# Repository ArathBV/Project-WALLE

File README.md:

# Project-WALLE
## Authors: Arath Villanueva, Devon Bolt
### Repository Overview
- This repository contains a folder of Doxygen items, WALL-E source code found in Codes, and Hardware Design aspects both mechanical and electrical in the Hardware folder.
### Project Website and Documentation
Project in depth details and website https://arathbv.github.io/Project-WALLE/index.html

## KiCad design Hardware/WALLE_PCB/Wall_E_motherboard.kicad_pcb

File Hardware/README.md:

# WALL-E Hardware Files
- This folder contains the Mechanical design files and the PCB design files. 
- The Mechanical desing components were changed based on the electronic and peripherals that were used for this WALL-E project.
- The WALL-E PCB Folder contains the WALL-E motheboard that was created for this project
- All original and remaining WALL-E CAD and step files can be found at https://wired.chillibasket.com/3d-printed-wall-e/

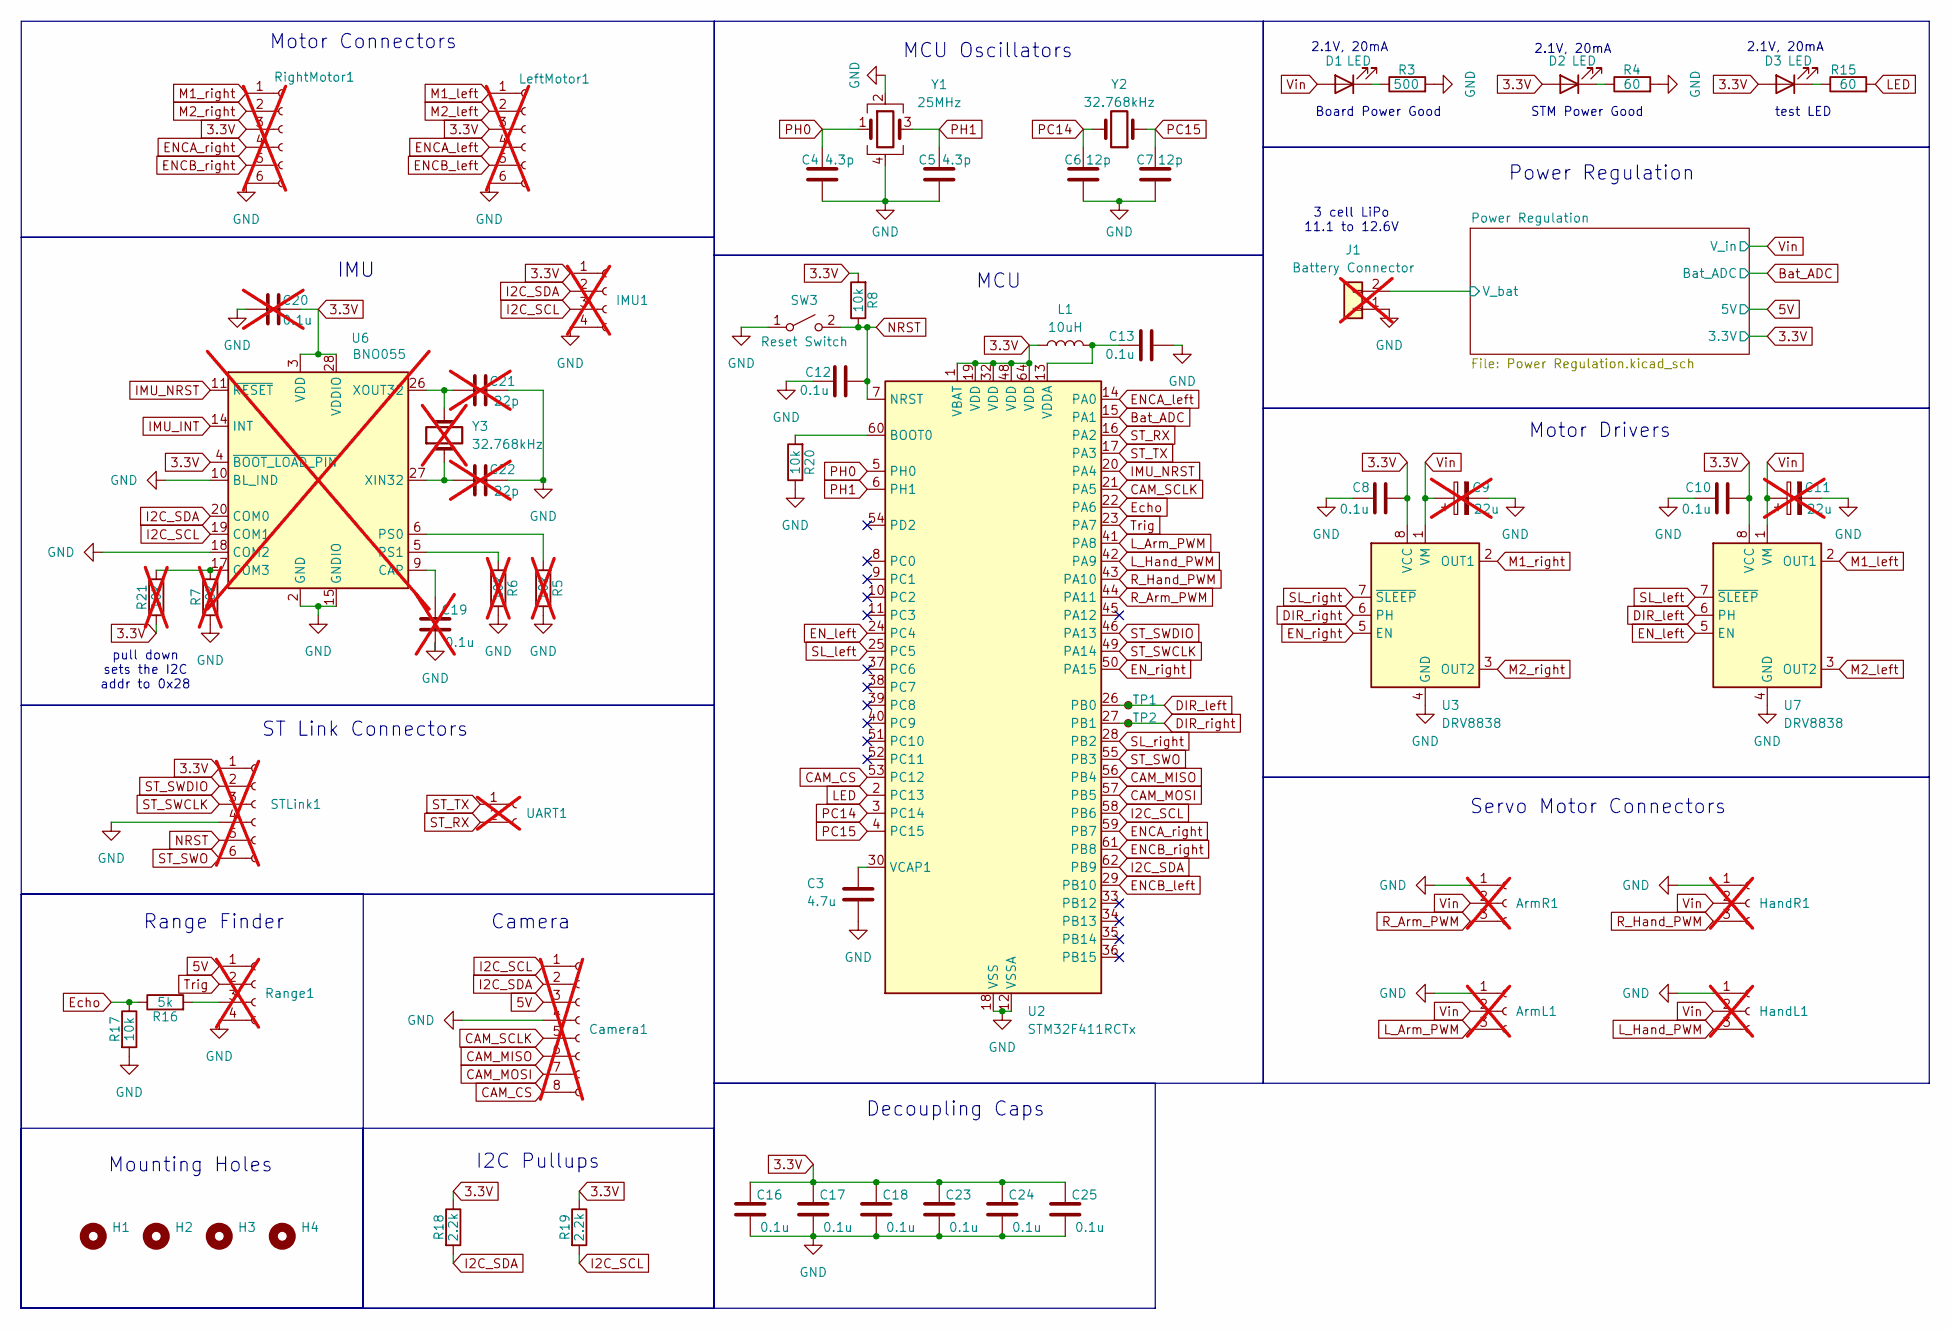
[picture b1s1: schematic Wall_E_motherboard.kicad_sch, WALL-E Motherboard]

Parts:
ArmL1: Conn_01x03_Socket; PinHeader_1x03_P2.54mm_Vertical; not fitted
ArmR1: Conn_01x03_Socket; PinHeader_1x03_P2.54mm_Vertical; not fitted
C3: 4.7u; C_0603_1608Metric
C4, C5: 4.3p; C_0603_1608Metric
C6, C7: 12p; C_0603_1608Metric
C8, C10, C12, C13, C16, C17, C18, C23, C24, C25: 0.1u; C_0603_1608Metric
C9, C11: 22u; CP_Radial_D5.0mm_P2.00mm; not fitted
C19, C20: 0.1u; C_0603_1608Metric; not fitted
C21, C22: 22p; C_0603_1608Metric; not fitted
Camera1: Conn_01x08_Socket; PinHeader_1x08_P2.54mm_Vertical; not fitted
D1, D2, D3: LED; LED_0603_1608Metric
H1, H2, H3, H4: MountingHole; MountingHole_3.2mm_M3
HandL1: Conn_01x03_Socket; PinHeader_1x03_P2.54mm_Vertical; not fitted
HandR1: Conn_01x03_Socket; PinHeader_1x03_P2.54mm_Vertical; not fitted
IMU1: Conn_01x04_Socket; PinHeader_1x04_P2.54mm_Vertical; not fitted
J1: Conn_01x02; AMASS_XT30PW-M_1x02_P2.50mm_Horizontal; not fitted
L1: 10uH; L_1008_2520Metric
LeftMotor1: Conn_01x06_Socket; PinHeader_1x06_P2.54mm_Vertical; not fitted
R3: 500; R_0603_1608Metric
R4, R15: 60; R_0603_1608Metric
R5, R6, R7, R21: 10k; R_0603_1608Metric; not fitted
R8, R17, R20: 10k; R_0603_1608Metric
R16: 5k; R_0603_1608Metric
R18, R19: 2.2k; R_0603_1608Metric
Range1: Conn_01x04_Socket; PinHeader_1x04_P2.54mm_Vertical; not fitted
RightMotor1: Conn_01x06_Socket; PinHeader_1x06_P2.54mm_Vertical; not fitted
STLink1: Conn_01x06_Socket; PinHeader_1x06_P2.54mm_Horizontal; not fitted
SW3: SW_SPST; SW_SPST_PTS645
TP1, TP2: TestPoint_Small; TestPoint_Pad_D1.0mm
U2: STM32F411RCTx; LQFP-64_10x10mm_P0.5mm
U3, U7: DRV8838; WSON-8-1EP_2x2mm_P0.5mm_EP0.9x1.6mm
U6: BNO055; LGA-28_5.2x3.8mm_P0.5mm; not fitted
UART1: Conn_01x02_Socket; PinHeader_1x02_P2.54mm_Horizontal; not fitted
Y1: 25MHz; Crystal_SMD_3225-4Pin_3.2x2.5mm
Y2: 32.768kHz; Crystal_SMD_3215-2Pin_3.2x1.5mm
Y3: 32.768kHz; Crystal_SMD_3215-2Pin_3.2x1.5mm; not fitted

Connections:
3.3V: C8.1, C10.1, C16.1, C17.1, C18.1, C20.2, C23.1, C24.1, C25.1, D2.2 (A), D3.2 (A), IMU1.1, L1.1, LeftMotor1.3, R8.2, R18.1, R19.1, R21.2, RightMotor1.3, STLink1.1, U2.1 (VBAT), U2.19 (VDD), U2.32 (VDD), U2.48 (VDD), U2.64 (VDD), U3.8 (VCC), U6.3 (VDD), U6.4 (~BOOT_LOAD_PIN), U6.28 (VDDIO), U7.8 (VCC); also elsewhere on the board
5V: Camera1.3, Range1.1; also elsewhere on the board
/Power Regulation/V_bat: J1.2; also elsewhere on the board
Bat_ADC: U2.15 (PA1); also elsewhere on the board
CAM_CS: Camera1.8, U2.53 (PC12)
CAM_MISO: Camera1.6, U2.56 (PB4)
CAM_MOSI: Camera1.7, U2.57 (PB5)
CAM_SCLK: Camera1.5, U2.21 (PA5)
DIR_left: TP1.1, U2.26 (PB0), U7.6 (PH)
DIR_right: TP2.1, U2.27 (PB1), U3.6 (PH)
ENCA_left: LeftMotor1.4, U2.14 (PA0)
ENCA_right: RightMotor1.4, U2.59 (PB7)
ENCB_left: LeftMotor1.5, U2.29 (PB10)
ENCB_right: RightMotor1.5, U2.61 (PB8)
EN_left: U2.24 (PC4), U7.5 (EN)
EN_right: U2.50 (PA15), U3.5 (EN)
Echo: R16.1, R17.1, U2.22 (PA6)
GND: ArmL1.1, ArmR1.1, C3.2, C4.2, C5.2, C6.2, C7.2, C8.2, C9.2, C10.2, C11.2, C12.2, C13.2, C16.2, C17.2, C18.2, C19.2, C20.1, C21.2, C22.2, C23.2, C24.2, C25.2, Camera1.4, HandL1.1, HandR1.1, IMU1.4, J1.1, LeftMotor1.6, R3.2, R4.2, R5.1, R6.1, R7.2, R17.2, R20.1, Range1.4, RightMotor1.6, STLink1.4, SW3.1 (A), U2.12 (VSSA), U2.18 (VSS), U2.31 (VSS), U2.47 (VSS), U2.63 (VSS), U3.4 (GND), U3.9 (GND), U6.2 (GND), U6.10 (BL_IND), U6.15 (GNDIO), U6.16 (GNDIO), U6.18 (COM2), U6.25 (GNDIO), U7.4 (GND), U7.9 (GND), Y1.2, Y1.4; also elsewhere on the board
I2C_SCL: Camera1.1, IMU1.3, R19.2, U2.58 (PB6), U6.19 (COM1)
I2C_SDA: Camera1.2, IMU1.2, R18.2, U2.62 (PB9), U6.20 (COM0)
IMU_INT: U6.14 (INT)
IMU_NRST: U2.20 (PA4), U6.11 (~RESET)
LED: R15.2, U2.2 (PC13)
L_Arm_PWM: ArmL1.3, U2.41 (PA8)
L_Hand_PWM: HandL1.3, U2.42 (PA9)
M1_left: LeftMotor1.1, U7.2 (OUT1)
M1_right: RightMotor1.1, U3.2 (OUT1)
M2_left: LeftMotor1.2, U7.3 (OUT2)
M2_right: RightMotor1.2, U3.3 (OUT2)
NRST: C12.1, R8.1, STLink1.5, SW3.2 (B), U2.7 (NRST)
unnamed: D1.1 (K), R3.1
unnamed: D2.1 (K), R4.1
unnamed: D3.1 (K), R15.1
unnamed: R16.2, Range1.3
unnamed: R20.2, U2.60 (BOOT0)
unnamed: C3.1, U2.30 (VCAP1)
unnamed: C13.1, L1.2, U2.13 (VDDA)
unnamed: C19.1, U6.9 (CAP)
unnamed: R7.1, R21.1, U6.17 (COM3)
unnamed: R5.2, U6.6 (PS0)
unnamed: R6.2, U6.5 (PS1)
unnamed: C22.1, U6.27 (XIN32), Y3.1
unnamed: C21.1, U6.26 (XOUT32), Y3.2
PC14: C6.1, U2.3 (PC14), Y2.2
PC15: C7.1, U2.4 (PC15), Y2.1
PH0: C4.1, U2.5 (PH0), Y1.1
PH1: C5.1, U2.6 (PH1), Y1.3
R_Arm_PWM: ArmR1.3, U2.44 (PA11)
R_Hand_PWM: HandR1.3, U2.43 (PA10)
SL_left: U2.25 (PC5), U7.7 (~SLEEP)
SL_right: U2.28 (PB2), U3.7 (~SLEEP)
ST_RX: U2.16 (PA2), UART1.2
ST_SWCLK: STLink1.3, U2.49 (PA14)
ST_SWDIO: STLink1.2, U2.46 (PA13)
ST_SWO: STLink1.6, U2.55 (PB3)
ST_TX: U2.17 (PA3), UART1.1
Trig: Range1.2, U2.23 (PA7)
Vin: ArmL1.2, ArmR1.2, C9.1, C11.1, D1.2 (A), HandL1.2, HandR1.2, U3.1 (VM), U7.1 (VM); also elsewhere on the board

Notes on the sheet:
Decoupling Caps
STM Power Good
Board Power Good
Range Finder
Power Regulation
Mounting Holes
Camera
MCU Oscillators
Motor Connectors
Servo Motor Connectors
ST Link Connectors
2.1V, 20mA
IMU
Motor Drivers
I2C Pullups
3 cell LiPo 11.1 to 12.6V
test LED
pull down sets the I2C addr to 0x28
MCU

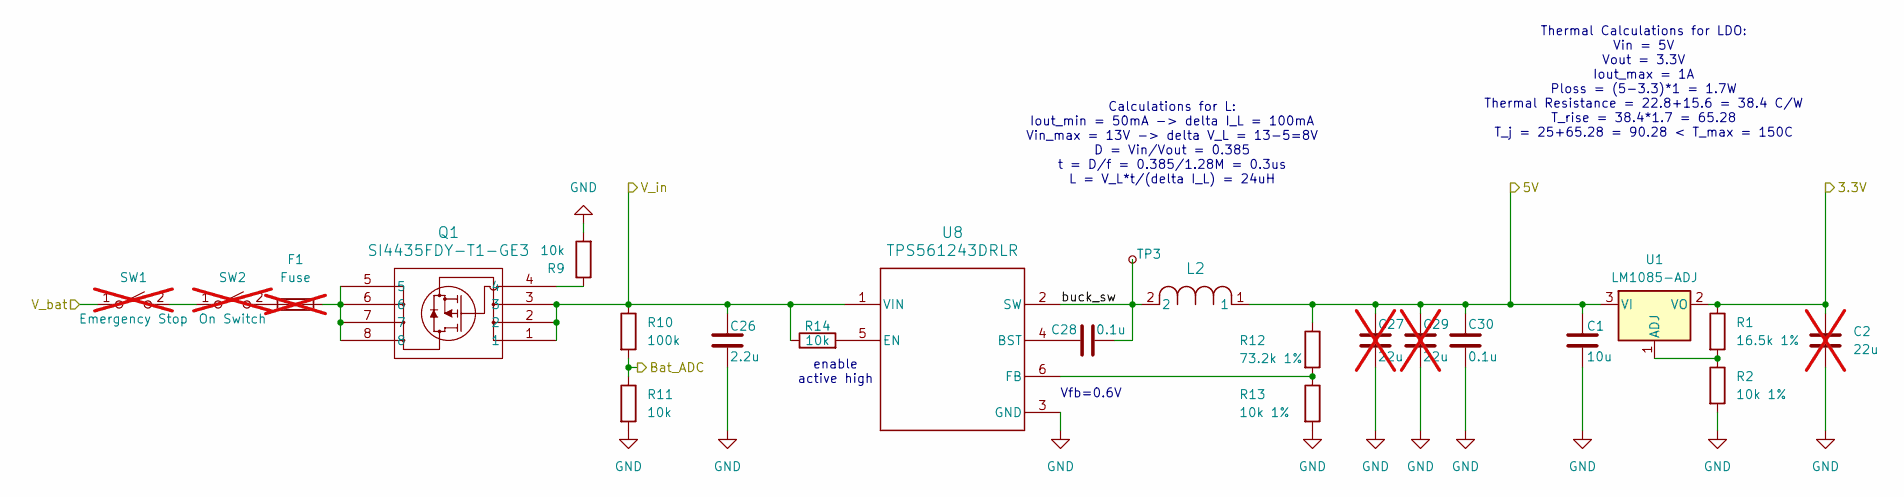
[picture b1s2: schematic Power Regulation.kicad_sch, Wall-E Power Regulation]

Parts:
C1: 10u; C_0603_1608Metric
C2, C27, C29: 22u; CP_Radial_D5.0mm_P2.00mm; not fitted
C26: 2.2u; C_0603_1608Metric
C28, C30: 0.1u; C_0603_1608Metric
F1: Fuse; Fuseholder_Blade_Mini_Keystone_3568; not fitted
L2: IFDC5050HZER270M; IND_IFDC5050HZER_VIS
Q1: SI4435FDY-T1-GE3; SO-8_VIS
R1: 16.5k 1%; R_0603_1608Metric
R2, R13: 10k 1%; R_0603_1608Metric
R9, R11, R14: 10k; R_0603_1608Metric
R10: 100k; R_0603_1608Metric
R12: 73.2k 1%; R_0603_1608Metric
SW1, SW2: SW_SPST; AMASS_XT30PW-F_1x02_P2.50mm_Horizontal; not fitted
TP3: TestPoint_Small; TestPoint_Pad_D1.0mm
U1: LM1085-ADJ; TO-263-3_TabPin2
U8: TPS561243DRLR; DRL0006A-MFG

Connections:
3.3V: C2.1, R1.1, U1.2 (VO); also elsewhere on the board
5V: C1.1, C27.1, C29.1, C30.1, L2.1, R12.1, U1.3 (VI); also elsewhere on the board
/Power Regulation/V_bat: SW1.1 (A); also elsewhere on the board
/Power Regulation/buck_sw: C28.2, L2.2, TP3.1, U8.2 (SW)
Bat_ADC: R10.2, R11.1; also elsewhere on the board
GND: C1.2, C2.2, C26.2, C27.2, C29.2, C30.2, R2.2, R9.2, R11.2, R13.2, U8.3 (GND); also elsewhere on the board
unnamed: F1.2, Q1.5, Q1.6, Q1.7, Q1.8
unnamed: Q1.4, R9.1
unnamed: SW1.2 (B), SW2.1 (A)
unnamed: F1.1, SW2.2 (B)
unnamed: R1.2, R2.1, U1.1 (ADJ)
unnamed: C28.1, U8.4 (BST)
unnamed: R14.2, U8.5 (EN)
unnamed: R12.2, R13.1, U8.6 (FB)
Vin: C26.1, Q1.1, Q1.2, Q1.3, R10.1, R14.1, U8.1 (VIN); also elsewhere on the board

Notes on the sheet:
Vfb=0.6V
Calculations for L: Iout_min = 50mA -> delta I_L = 100mA Vin_max = 13V -> delta V_L = 13-5=8V D = Vin/Vout = 0.385 t = D/f = 0.385/1.28M = 0.3us L = V_L*t/(delta I_L) = 24uH
enable active high
Thermal Calculations for LDO: Vin = 5V Vout = 3.3V Iout_max = 1A Ploss = (5-3.3)*1 = 1.7W Thermal Resistance = 22.8+15.6 = 38.4 C/W T_rise = 38.4*1.7 = 65.28 T_j = 25+65.28 = 90.28 < T_max = 150C

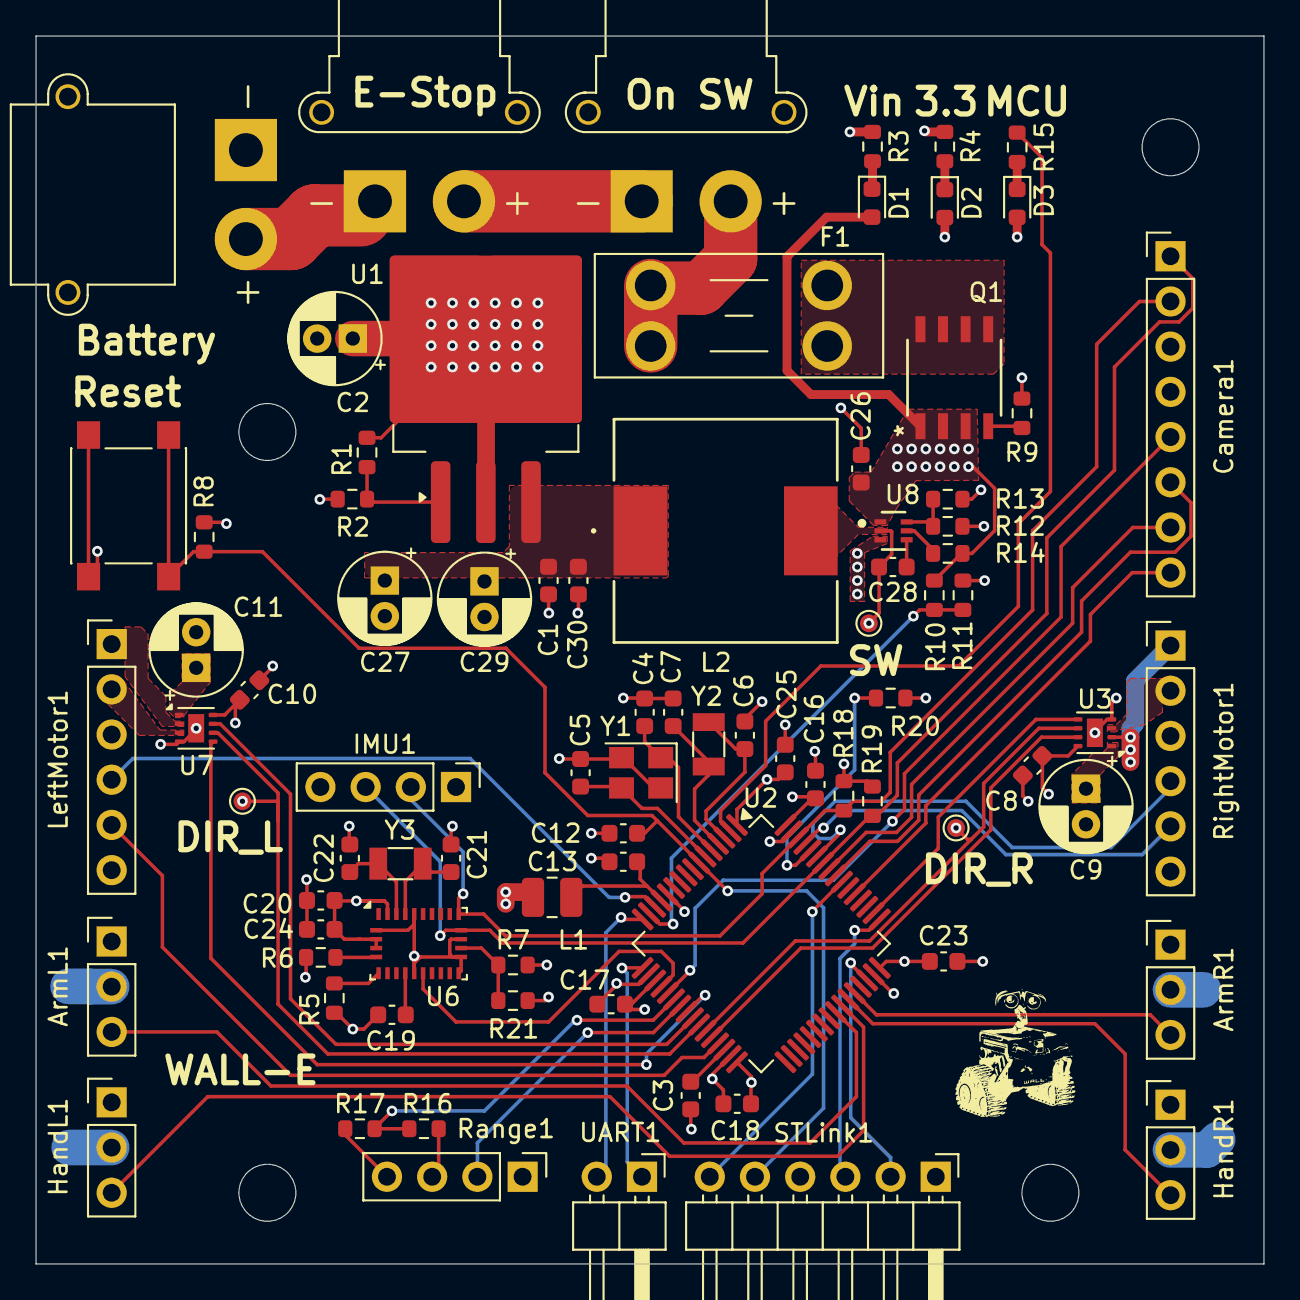
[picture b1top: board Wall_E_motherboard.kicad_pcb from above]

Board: 4 copper layers, 69.0 x 69.0 mm, 87 parts (0 on the bottom side), 66 nets.

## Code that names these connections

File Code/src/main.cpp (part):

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UART_HandleTypeDef huart2;

/*Global Motors for interrupt updates*/
RomiMotor rightMotor(GPIOA, EN_Right_Pin, GPIOB, DIR_Right_Pin, GPIOB, SL_Right_Pin);
RomiMotor leftMotor(GPIOC, EN_Left_Pin, GPIOB, DIR_Left_Pin, GPIOC, SL_Left_Pin);
/* USER CODE BEGIN PV */

/* USER CODE END PV */
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
  /*Peripherals Instantiation*/
  BatteryMonitor batteryMonitor(&hadc1, 7000);
  HCSR04 rangeFinder(GPIOA, Trig_Pin, Echo_GPIO_Port, Echo_Pin, &htim3);
  BNO055 imu(&hi2c1, (uint8_t) 0x28);
  OV2640Camera camera(&hi2c1, &hspi1, GPIOC, CAM_CS_Pin);
  Servo rightArm(&htim1, TIM_CHANNEL_4);
  Servo rightHand(&htim1, TIM_CHANNEL_3);
  Servo leftArm(&htim1, TIM_CHANNEL_1);
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  __HAL_RCC_GPIOB_CLK_ENABLE();

  /*Configure GPIO pin Output Level */
  HAL_GPIO_WritePin(GPIOC, LED_PIN_Pin|EN_Left_Pin|SL_Left_Pin|CAM_CS_Pin, GPIO_PIN_RESET);

  /*Configure GPIO pin Output Level */
  HAL_GPIO_WritePin(GPIOA, IMU_NRST_Pin|Trig_Pin|EN_Right_Pin, GPIO_PIN_RESET);

  /*Configure GPIO pin Output Level */
  HAL_GPIO_WritePin(GPIOB, DIR_Left_Pin|DIR_Right_Pin|SL_Right_Pin, GPIO_PIN_RESET);

  /*Configure GPIO pins : LED_PIN_Pin EN_Left_Pin SL_Left_Pin CAM_CS_Pin */
  GPIO_InitStruct.Pin = LED_PIN_Pin|EN_Left_Pin|SL_Left_Pin|CAM_CS_Pin;
  GPIO_InitStruct.Mode = GPIO_MODE_OUTPUT_PP;
  GPIO_InitStruct.Pull = GPIO_NOPULL;
  GPIO_InitStruct.Speed = GPIO_SPEED_FREQ_LOW;
  HAL_GPIO_Init(GPIOC, &GPIO_InitStruct);

  /*Configure GPIO pins : IMU_NRST_Pin Trig_Pin EN_Right_Pin */
  GPIO_InitStruct.Pin = IMU_NRST_Pin|Trig_Pin|EN_Right_Pin;
  GPIO_InitStruct.Mode = GPIO_MODE_OUTPUT_PP;
  GPIO_InitStruct.Pull = GPIO_NOPULL;
  GPIO_InitStruct.Speed = GPIO_SPEED_FREQ_LOW;
  HAL_GPIO_Init(GPIOA, &GPIO_InitStruct);

  /*Configure GPIO pin : Echo_Pin */
  GPIO_InitStruct.Pin = Echo_Pin;
  GPIO_InitStruct.Mode = GPIO_MODE_INPUT;
  GPIO_InitStruct.Pull = GPIO_NOPULL;
  HAL_GPIO_Init(Echo_GPIO_Port, &GPIO_InitStruct);

  /*Configure GPIO pins : DIR_Left_Pin DIR_Right_Pin SL_Right_Pin */
  GPIO_InitStruct.Pin = DIR_Left_Pin|DIR_Right_Pin|SL_Right_Pin;
  GPIO_InitStruct.Mode = GPIO_MODE_OUTPUT_PP;
  GPIO_InitStruct.Pull = GPIO_NOPULL;
  GPIO_InitStruct.Speed = GPIO_SPEED_FREQ_LOW;
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
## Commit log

2025-06-13 Final WALLE Files
2025-06-13 Header Files for WALLE
2025-06-13 Commented Camera Files
2025-06-13 WALLE ioc file
2025-06-14 WALLE PCB Folder
2025-06-14 WALL-E Modified Step Files
2025-06-14 README updates on the Code section
2025-06-14 Updated Comments
2025-06-14 Updated BNO documentation
2025-06-14 Updated and Commented files for Doxygen formatting
2025-06-14 Doxygen Items and Files
2025-06-14 Mechanical Design Report
2025-06-14 Photos and Updates
2025-06-14 Mechanical Page Done
2025-06-14 Sensor Page Complete
2025-06-14 Moved to docs
2025-06-14 Site Changes
2025-06-14 Updated Tabs
2025-06-14 Updated Electrical Design and GitRepo cleanup

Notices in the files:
Code/src/main.cpp:
Copyright (c) 2025 STMicroelectronics.
All rights reserved.
This software is licensed under terms that can be found in the LICENSE file
